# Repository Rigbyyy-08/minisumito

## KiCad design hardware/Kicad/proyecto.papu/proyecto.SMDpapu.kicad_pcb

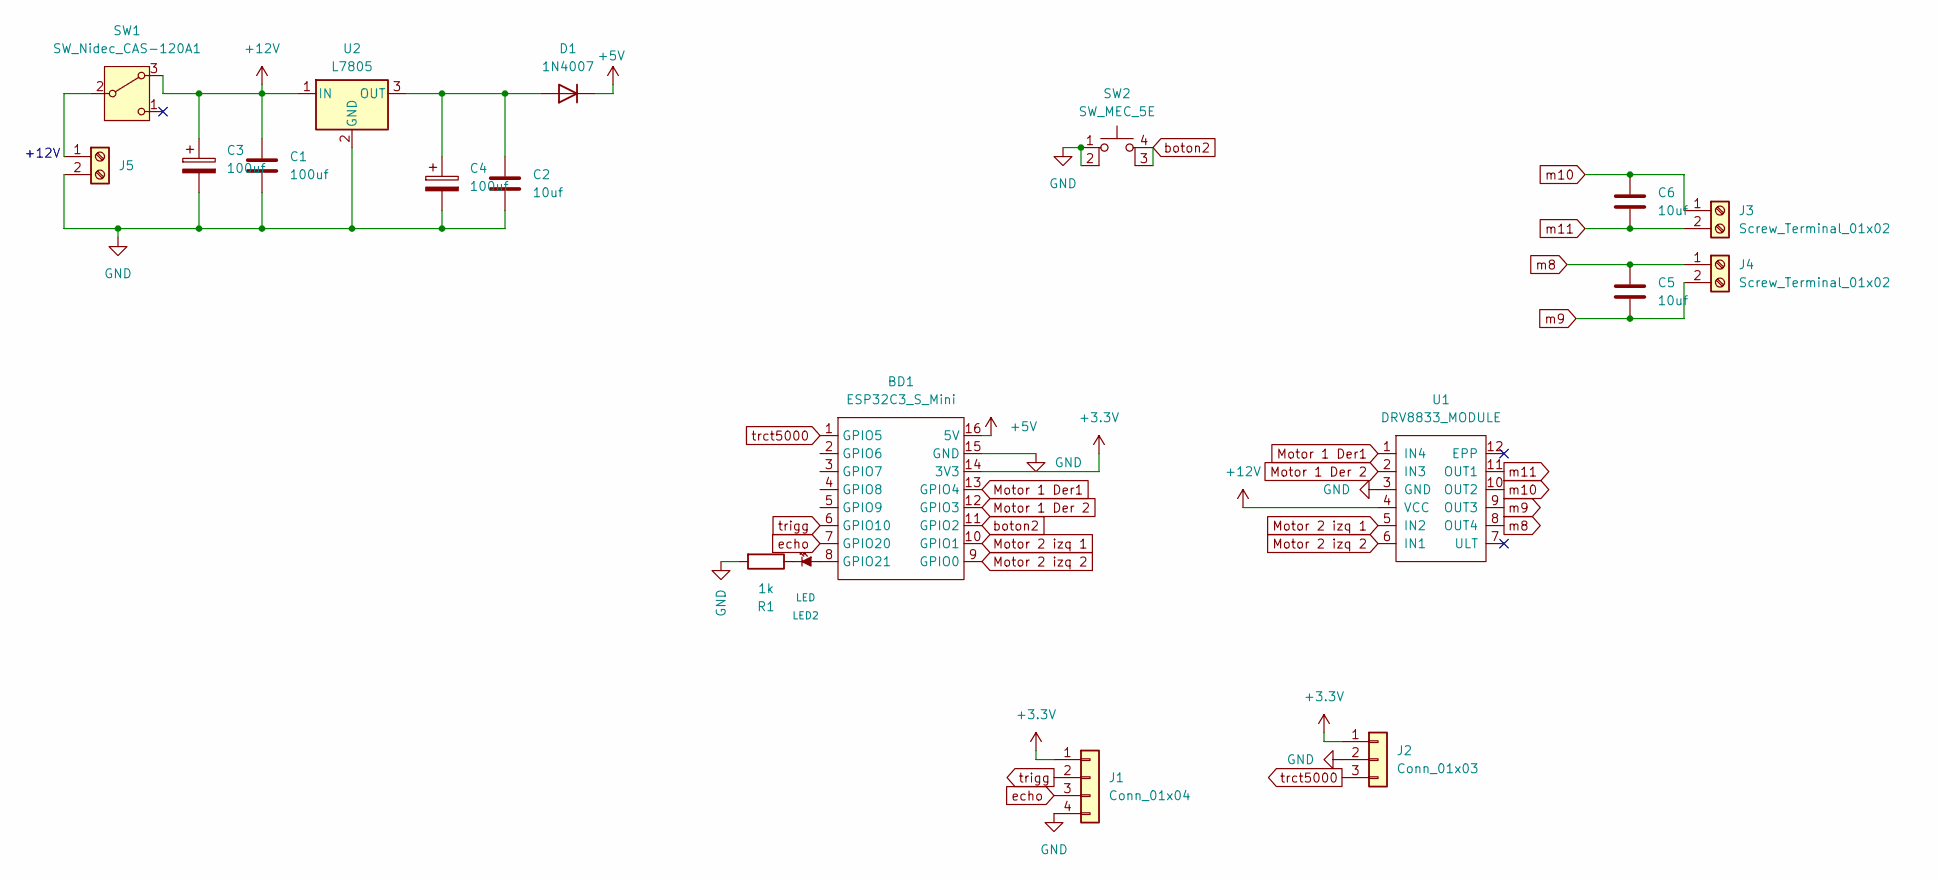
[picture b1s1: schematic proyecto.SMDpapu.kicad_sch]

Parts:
BD1: ESP32C3_S_Mini; ESP32_C3_SM
C1: 100uf; C_0805_2012Metric
C2, C5, C6: 10uf; C_0805_2012Metric
C3, C4: 100uf; C_Radial_D6.3mm_H5.0mm_P2.50mm
D1: 1N4007; D_SMA
J1: Conn_01x04; PinHeader_1x04_P2.54mm_Vertical
J2: Conn_01x03; PinHeader_1x03_P2.54mm_Vertical
J3, J4, J5: Screw_Terminal_01x02; TerminalBlock_MaiXu_MX126-5.0-02P_1x02_P5.00mm
LED2: LED; LED_D5.0mm
R1: 1k; R_0805_2012Metric
SW1: SW_Nidec_CAS-120A1; SW_SPDT_TH_Vertical
SW2: SW_MEC_5E; PUSH_SWITCH_THT
U1: DRV8833_MODULE
U2: L7805; TO-263-3_TabPin2

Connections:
+3.3V: BD1.14 (3V3), J1.1, J2.1
+5V: BD1.16 (5V), D1.1 (K)
+12V: C1.1, C3.1, SW1.3 (A), U1.4 (VCC), U2.1 (IN)
GND: BD1.15 (GND), C1.2, C2.2, C3.2, C4.2, J1.4, J2.2, J5.2, R1.2, SW2.1, SW2.2, U1.3 (GND), U2.2 (GND)
Motor 1 Der1: BD1.13 (GPIO4), U1.1 (IN4)
Motor 1 Der 2: BD1.12 (GPIO3), U1.2 (IN3)
Motor 2 izq 1: BD1.10 (GPIO1), U1.5 (IN2)
Motor 2 izq 2: BD1.9 (GPIO0), U1.6 (IN1)
unnamed: BD1.8 (GPIO21), LED2.1 (A)
unnamed: C2.1, C4.1, D1.2 (A), U2.3 (OUT)
unnamed: J5.1, SW1.2 (B)
unnamed: LED2.2 (K), R1.1
boton2: BD1.11 (GPIO2), SW2.3 (K), SW2.4 (A)
echo: BD1.7 (GPIO20), J1.3
m8: C5.1, J4.1, U1.8 (OUT4)
m9: C5.2, J4.2, U1.9 (OUT3)
m10: C6.1, J3.1, U1.10 (OUT2)
m11: C6.2, J3.2, U1.11 (OUT1)
trct5000: BD1.1 (GPIO5), J2.3
trigg: BD1.6 (GPIO10), J1.2

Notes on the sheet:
+12V

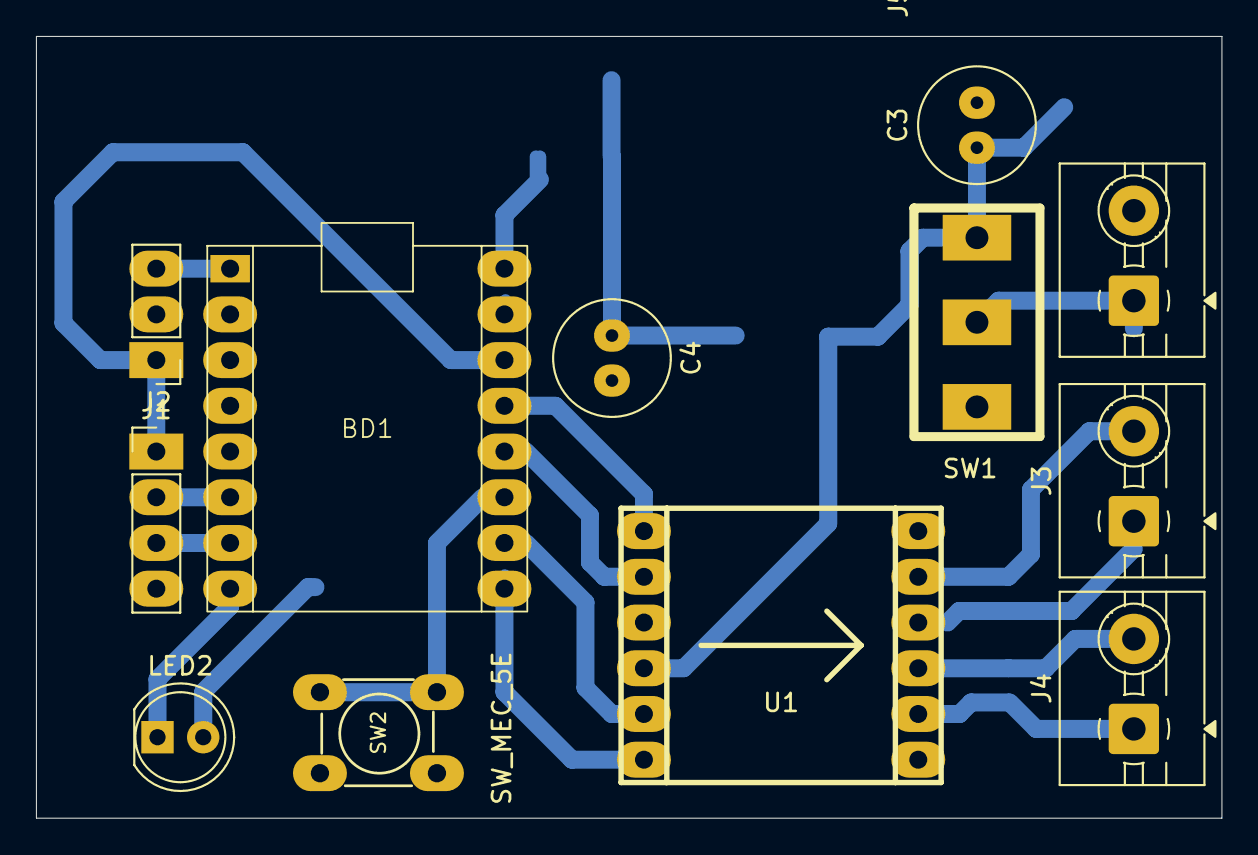
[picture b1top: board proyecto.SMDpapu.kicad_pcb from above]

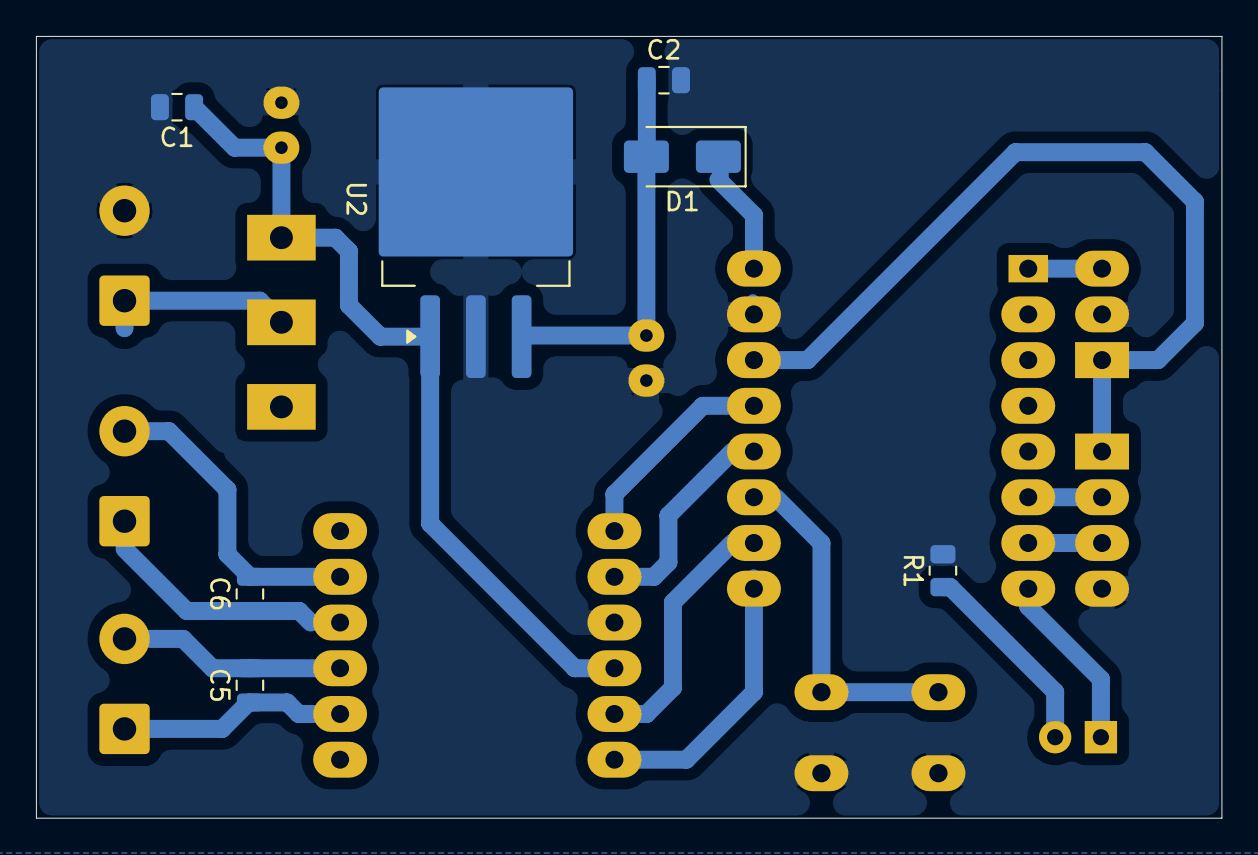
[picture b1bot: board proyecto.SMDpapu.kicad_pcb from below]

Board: 2 copper layers, 65.9 x 43.4 mm, 19 parts (7 on the bottom side), 20 nets.

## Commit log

2026-04-20 Se agregaron carpetas y PCB
2026-04-20 se termino pcb
